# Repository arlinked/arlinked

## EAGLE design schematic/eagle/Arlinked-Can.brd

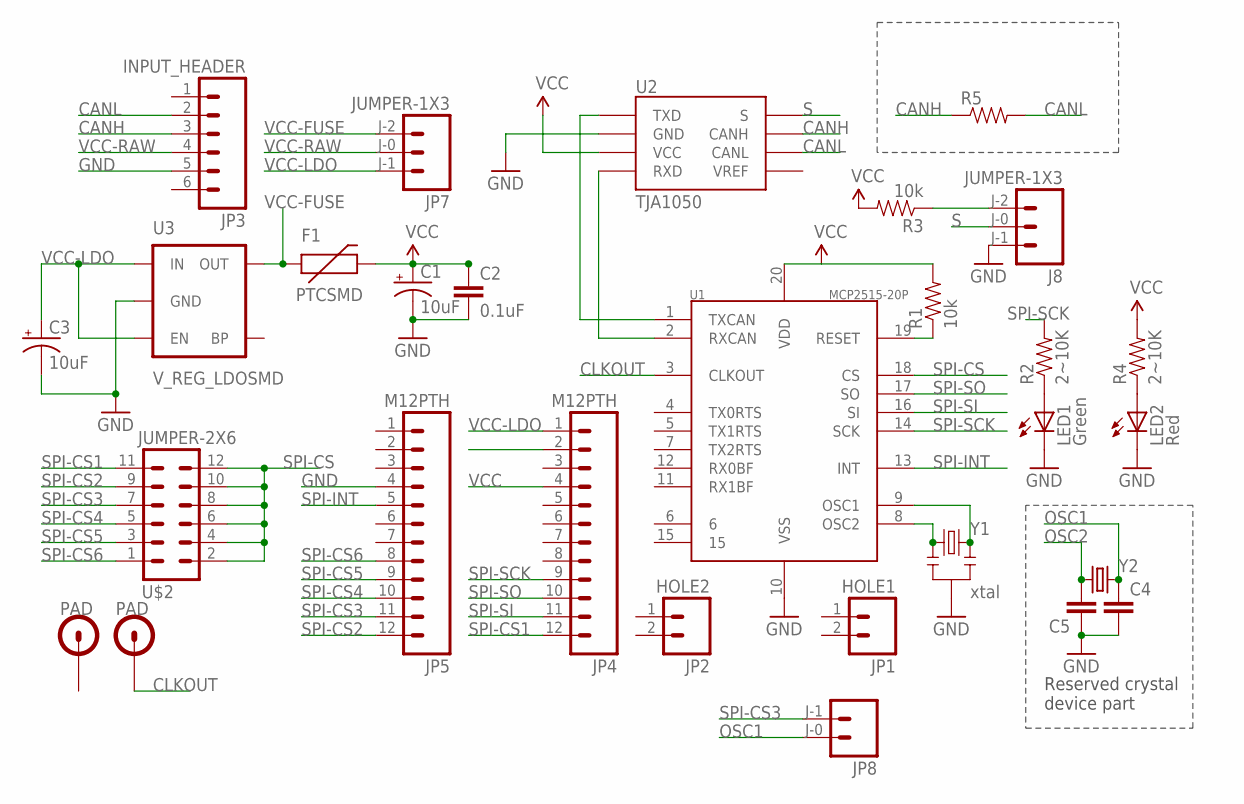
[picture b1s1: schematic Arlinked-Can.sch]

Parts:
C1, C3: 10uF; EIA3216
C2: 0.1uF; 0402-CAP
C4, C5: CAP0402-CAP; 0402-CAP
F1: PTCSMD; PTC-1206
J8: JUMPER-1X3; JUMPER-1X3-SMD-10
JP1: HOLE1; 1X02
JP2: HOLE2; 1X02
JP3: INPUT_HEADER; 1X06
JP4, JP5: M12PTH; 1X12
JP7: JUMPER-1X3; JUMPER-1X3-SMD-10
JP8: JUMPER-1X2; JUMPER-1X2-SMD-10
LED1: Green; LED-0603
LED2: Red; LED-0603
R1, R3: 10k; 0603-RES
R2, R4: 2~10K; 0402-RES
R5: RESISTOR0603-RES; 0603-RES
U1: MCP2515-20P; TSSOP20
U2: TJA1050; SOIC-8
U3: V_REG_LDOSMD; SOT23-5
U$1: PAD; PAD-HOLE-4MM
U$2: JUMPER-2X6; JUMPER-2X06-SMD
U$3: PAD_SMD; PAD-SMD-2MM
Y1: xtal; RESONATOR-SMD
Y2: CRYSTALPAD-ONLY; HC49U-V

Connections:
CANH: JP3.3, R5.1, U2.7 (CANH)
CANL: JP3.2, R5.2, U2.6 (CANL)
CLKOUT: U1.3 (CLKOUT), U$3.P$1
GND: C1.C (-), C2.2, C3.C (-), C4.2, C5.1, J8.J-1, JP3.5, JP4.2, JP5.4, LED1.C, LED2.C, U1.10 (VSS), U2.2 (GND), U3.2 (GND), Y1.2
LED1-CAN-2: LED1.A, R2.1
LED2-POWER-2: LED2.A, R4.1
unnamed: U1.1 (TXCAN), U2.1 (TXD)
unnamed: U1.2 (RXCAN), U2.4 (RXD)
unnamed: R1.1, U1.19 (RESET)
unnamed: J8.J-2, R3.1
OSC1: C4.1, JP8.J-0 (J-1), U1.9 (OSC1), Y1.3, Y2.2
OSC2: C5.2, U1.8 (OSC2), Y1.1, Y2.1
S: J8.J-0, U2.8 (S)
SPI-CS: U1.18 (CS), U$2.2, U$2.4, U$2.6, U$2.8, U$2.10, U$2.12
SPI-CS1: JP4.12, U$2.11
SPI-CS2: JP5.12, U$2.9
SPI-CS3: JP5.11, JP8.J-1 (J-0), U$2.7
SPI-CS4: JP5.10, U$2.5
SPI-CS5: JP5.9, U$2.3
SPI-CS6: JP5.8, U$2.1
SPI-INT: JP5.5, U1.13 (INT)
SPI-SCK: JP4.9, R2.2, U1.14 (SCK)
SPI-SI: JP4.11, U1.16 (SI)
SPI-SO: JP4.10, U1.17 (SO)
VCC: C1.A (+), C2.1, F1.2, JP4.4, R1.2, R3.2, R4.2, U1.20 (VDD), U2.3 (VCC)
VCC-FUSE: F1.1, JP7.J-2, U3.5 (OUT)
VCC-LDO: C3.A (+), JP4.1, JP7.J-1, U3.1 (IN), U3.3 (EN)
VCC-RAW: JP3.4, JP7.J-0

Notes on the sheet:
Reserved crystal device part

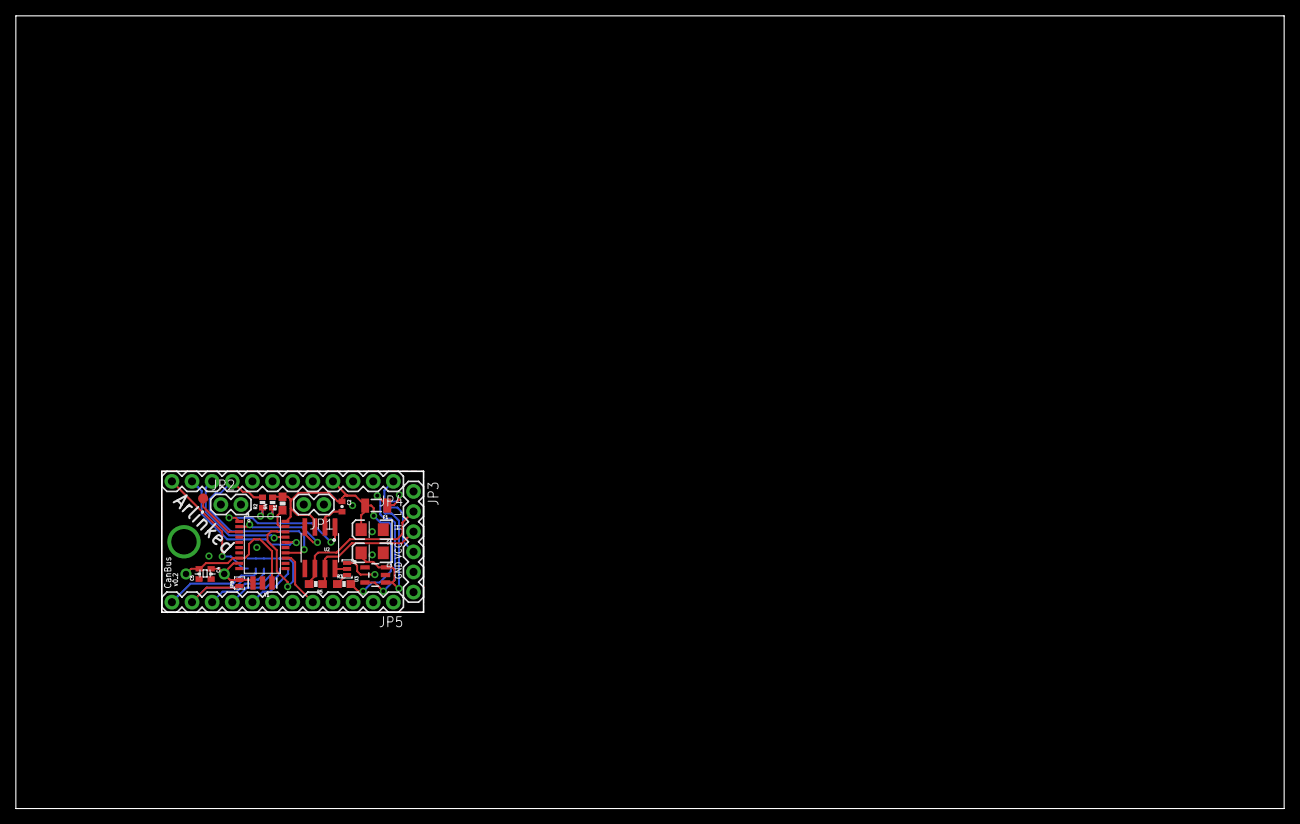
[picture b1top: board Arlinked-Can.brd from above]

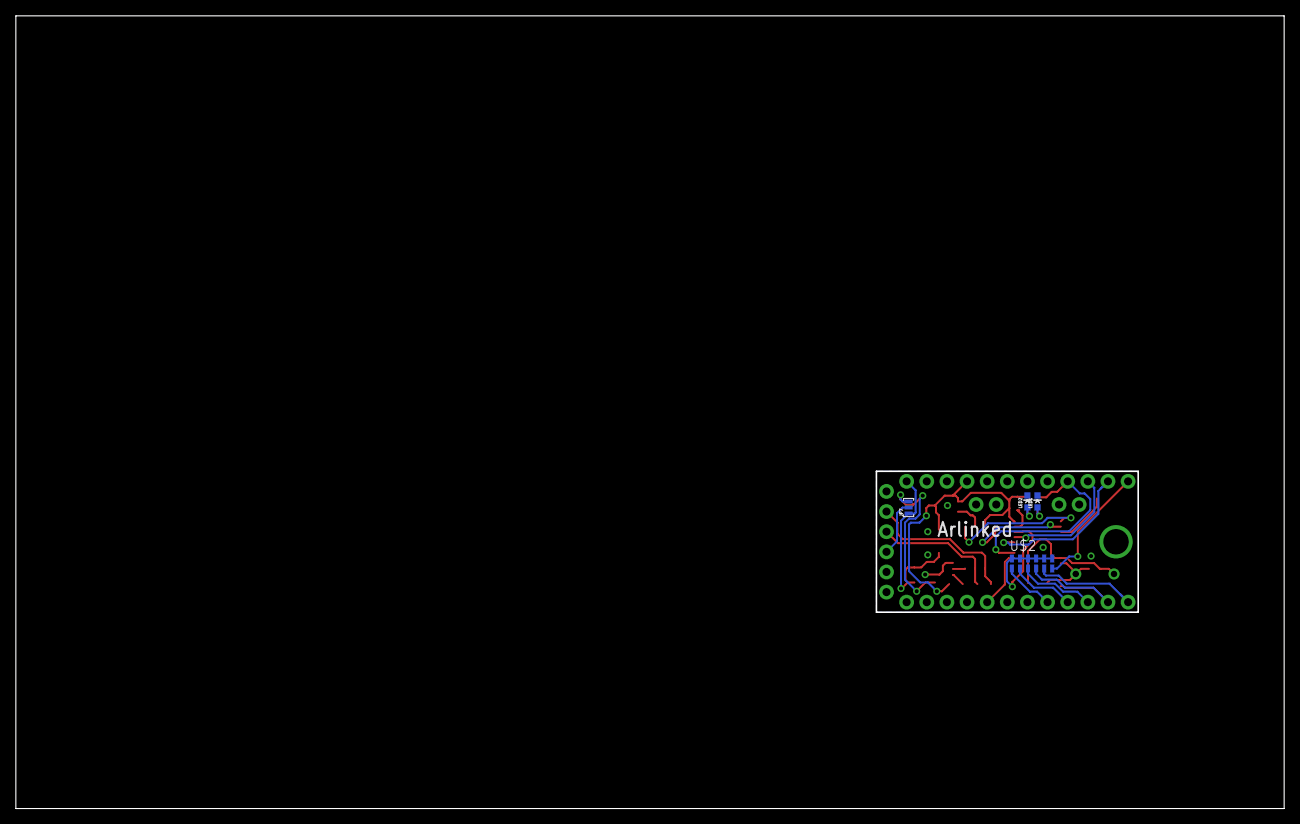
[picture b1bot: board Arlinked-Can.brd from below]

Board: 2 copper layers, 160.0 x 100.0 mm, 29 parts (4 on the bottom side), 28 nets.

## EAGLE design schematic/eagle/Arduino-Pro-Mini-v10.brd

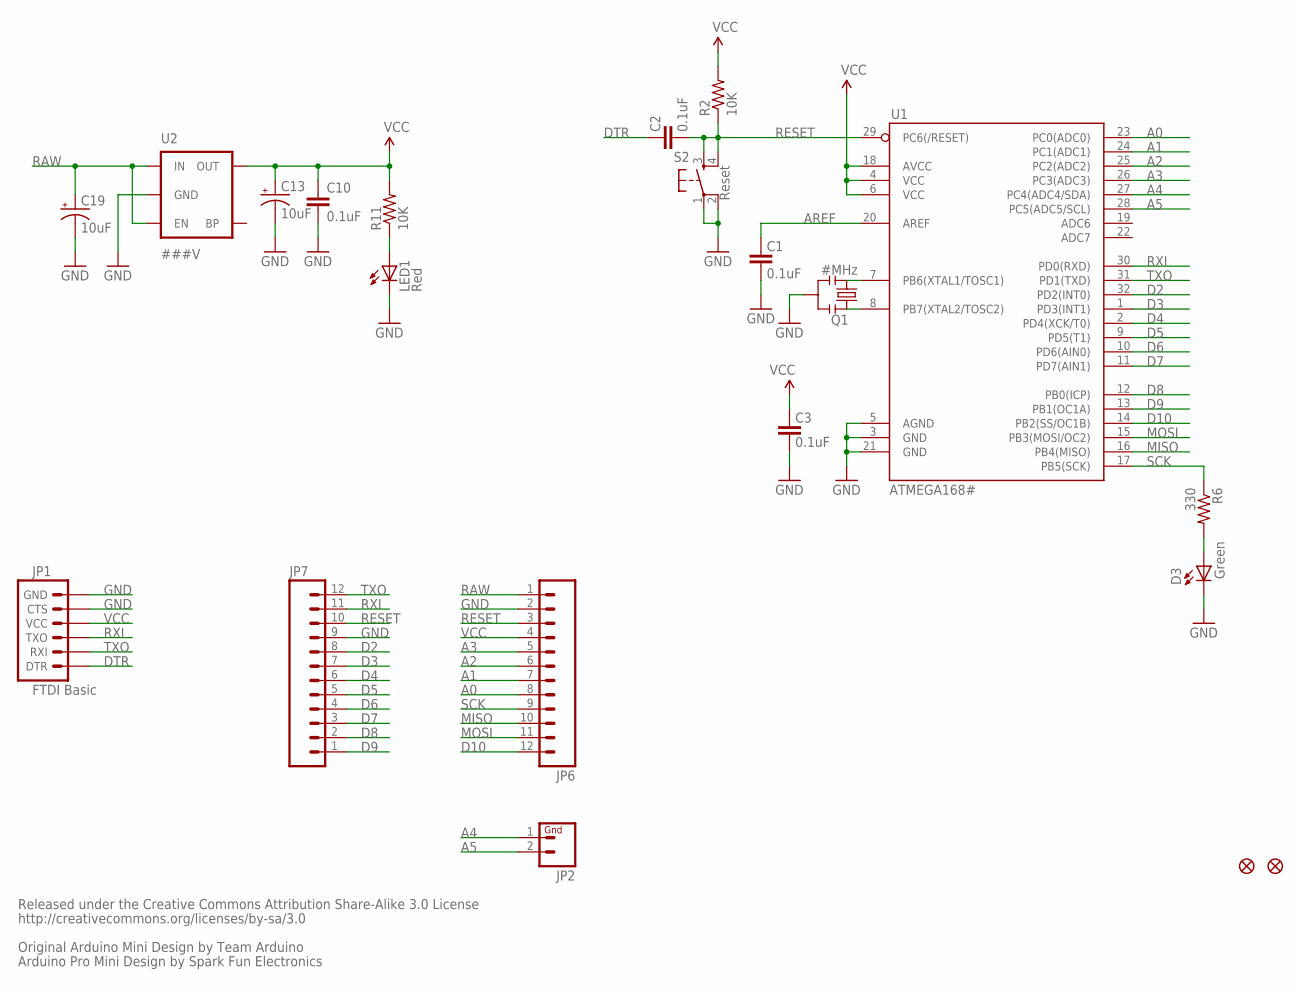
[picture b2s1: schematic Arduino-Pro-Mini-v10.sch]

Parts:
C1, C2, C3, C10: 0.1uF; C0402
C13, C19: 10uF; EIA3216
D3: Green; LED-0603
JP1: FTDI Basic; 1X06
JP2: M02PTH; 1X02
JP6, JP7: M12PTH; 1X12
LED1: Red; LED-0603
Q1: #MHz; RESONATOR-SMD
R2, R11: 10K; C0402
R6: 330; C0402
S2: Reset; TACTILE_SWITCH_SMD
U1: ATMEGA168#; TQFP32-08
U2: ###V; SOT23-5
U$2, U$4: FIDUCIAL1X2; FIDUCIAL-1X2

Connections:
A0: JP6.8, U1.23 (PC0(ADC0))
A1: JP6.7, U1.24 (PC1(ADC1))
A2: JP6.6, U1.25 (PC2(ADC2))
A3: JP6.5, U1.26 (PC3(ADC3))
A4: JP2.1, U1.27 (PC4(ADC4/SDA))
A5: JP2.2, U1.28 (PC5(ADC5/SCL))
AREF: C1.2, U1.20 (AREF)
D2: JP7.8, U1.32 (PD2(INT0))
D3: JP7.7, U1.1 (PD3(INT1))
D4: JP7.6, U1.2 (PD4(XCK/T0))
D5: JP7.5, U1.9 (PD5(T1))
D6: JP7.4, U1.10 (PD6(AIN0))
D7: JP7.3, U1.11 (PD7(AIN1))
D8: JP7.2, U1.12 (PB0(ICP))
D9: JP7.1, U1.13 (PB1(OC1A))
D10: JP6.12, U1.14 (PB2(SS/OC1B))
DTR: C2.2, JP1.1 (DTR)
GND: C1.1, C3.1, C10.2, C13.C (-), C19.C (-), D3.C, JP1.5 (CTS), JP1.6 (GND), JP6.2, JP7.9, LED1.C, Q1.2, S2.1, S2.2, U1.3 (GND), U1.5 (AGND), U1.21 (GND), U2.2 (GND)
MISO: JP6.10, U1.16 (PB4(MISO))
MOSI: JP6.11, U1.15 (PB3(MOSI/OC2))
unnamed: Q1.1, U1.8 (PB7(XTAL2/TOSC2))
unnamed: Q1.3, U1.7 (PB6(XTAL1/TOSC1))
unnamed: D3.A, R6.2
unnamed: LED1.A, R11.1
RAW: C19.A (+), JP6.1, U2.1 (IN), U2.3 (EN)
RESET: C2.1, JP6.3, JP7.10, R2.1, S2.3, S2.4, U1.29 (PC6(/RESET))
RXI: JP1.3 (TXO), JP7.11, U1.30 (PD0(RXD))
SCK: JP6.9, R6.1, U1.17 (PB5(SCK))
TXO: JP1.2 (RXI), JP7.12, U1.31 (PD1(TXD))
VCC: C3.2, C10.1, C13.A (+), JP1.4 (VCC), JP6.4, R2.2, R11.2, U1.4 (VCC), U1.6 (VCC), U1.18 (AVCC), U2.5 (OUT)

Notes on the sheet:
Released under the Creative Commons Attribution Share-Alike 3.0 License
http://creativecommons.org/licenses/by-sa/3.0
Original Arduino Mini Design by Team Arduino
Arduino Pro Mini Design by Spark Fun Electronics

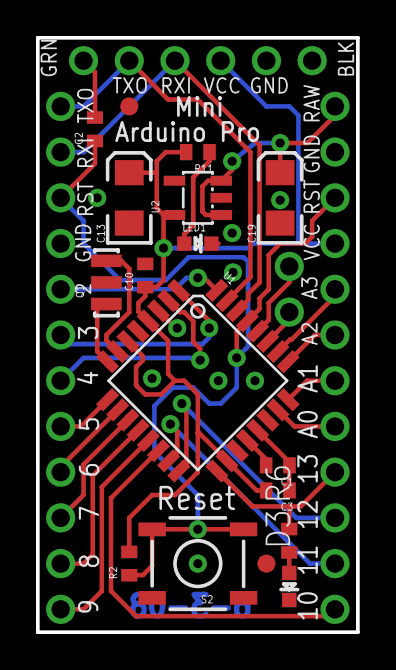
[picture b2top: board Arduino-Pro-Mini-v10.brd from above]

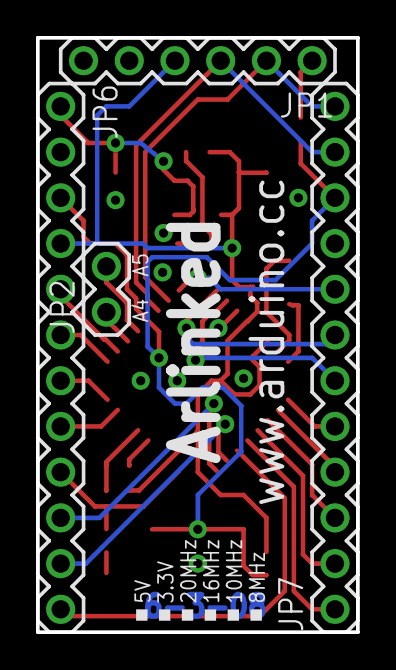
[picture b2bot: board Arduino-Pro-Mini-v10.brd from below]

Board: 2 copper layers, 17.8 x 33.0 mm, 21 parts (4 on the bottom side), 30 nets.

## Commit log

2014-03-28 move to schematic/eagle
2014-03-31 Add Cygwin makefile support
2014-04-01 Add .ino file support
2014-04-01 Add upload support
2014-04-03 Add can support and a client program that will sleep when can-bus idle
2014-04-03 Add install support for mk
2014-04-03 Move mcp2515 to can
2014-04-04 Add sleep support when can-bus idle
2014-04-04 MCP2515 sleeps when can-bus idle to save upto 3/4 power.
2014-04-04 Bug fixed: dead loop
2014-04-04 #2: CCanMessage constructor param nLen should limit the length of array copying; Bug fixed in CCanMcp2515Impl::write_canMsg
2014-04-05 Fixed compile error
2014-04-06 Fixed complie error
2014-04-08 Update schematic of Arduino Pro Mini
2014-04-08 Added Arduino Pro Mini v13
2014-04-09 Add Can-bus schematic
2014-04-10 Added schematic/protel/arlinked-can-v0.1-print-10p.pcb
2014-04-10 Added Arlinked CanBus module v0.2
2014-04-17 CanBus module v0.2 schematic and PCB release #4 fixed Vdd Vss mistake

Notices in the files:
parts and their libraries:
SparkFun: Licensing: CC v3.0 Share-Alike You are welcome to use this library for commercial purposes.
